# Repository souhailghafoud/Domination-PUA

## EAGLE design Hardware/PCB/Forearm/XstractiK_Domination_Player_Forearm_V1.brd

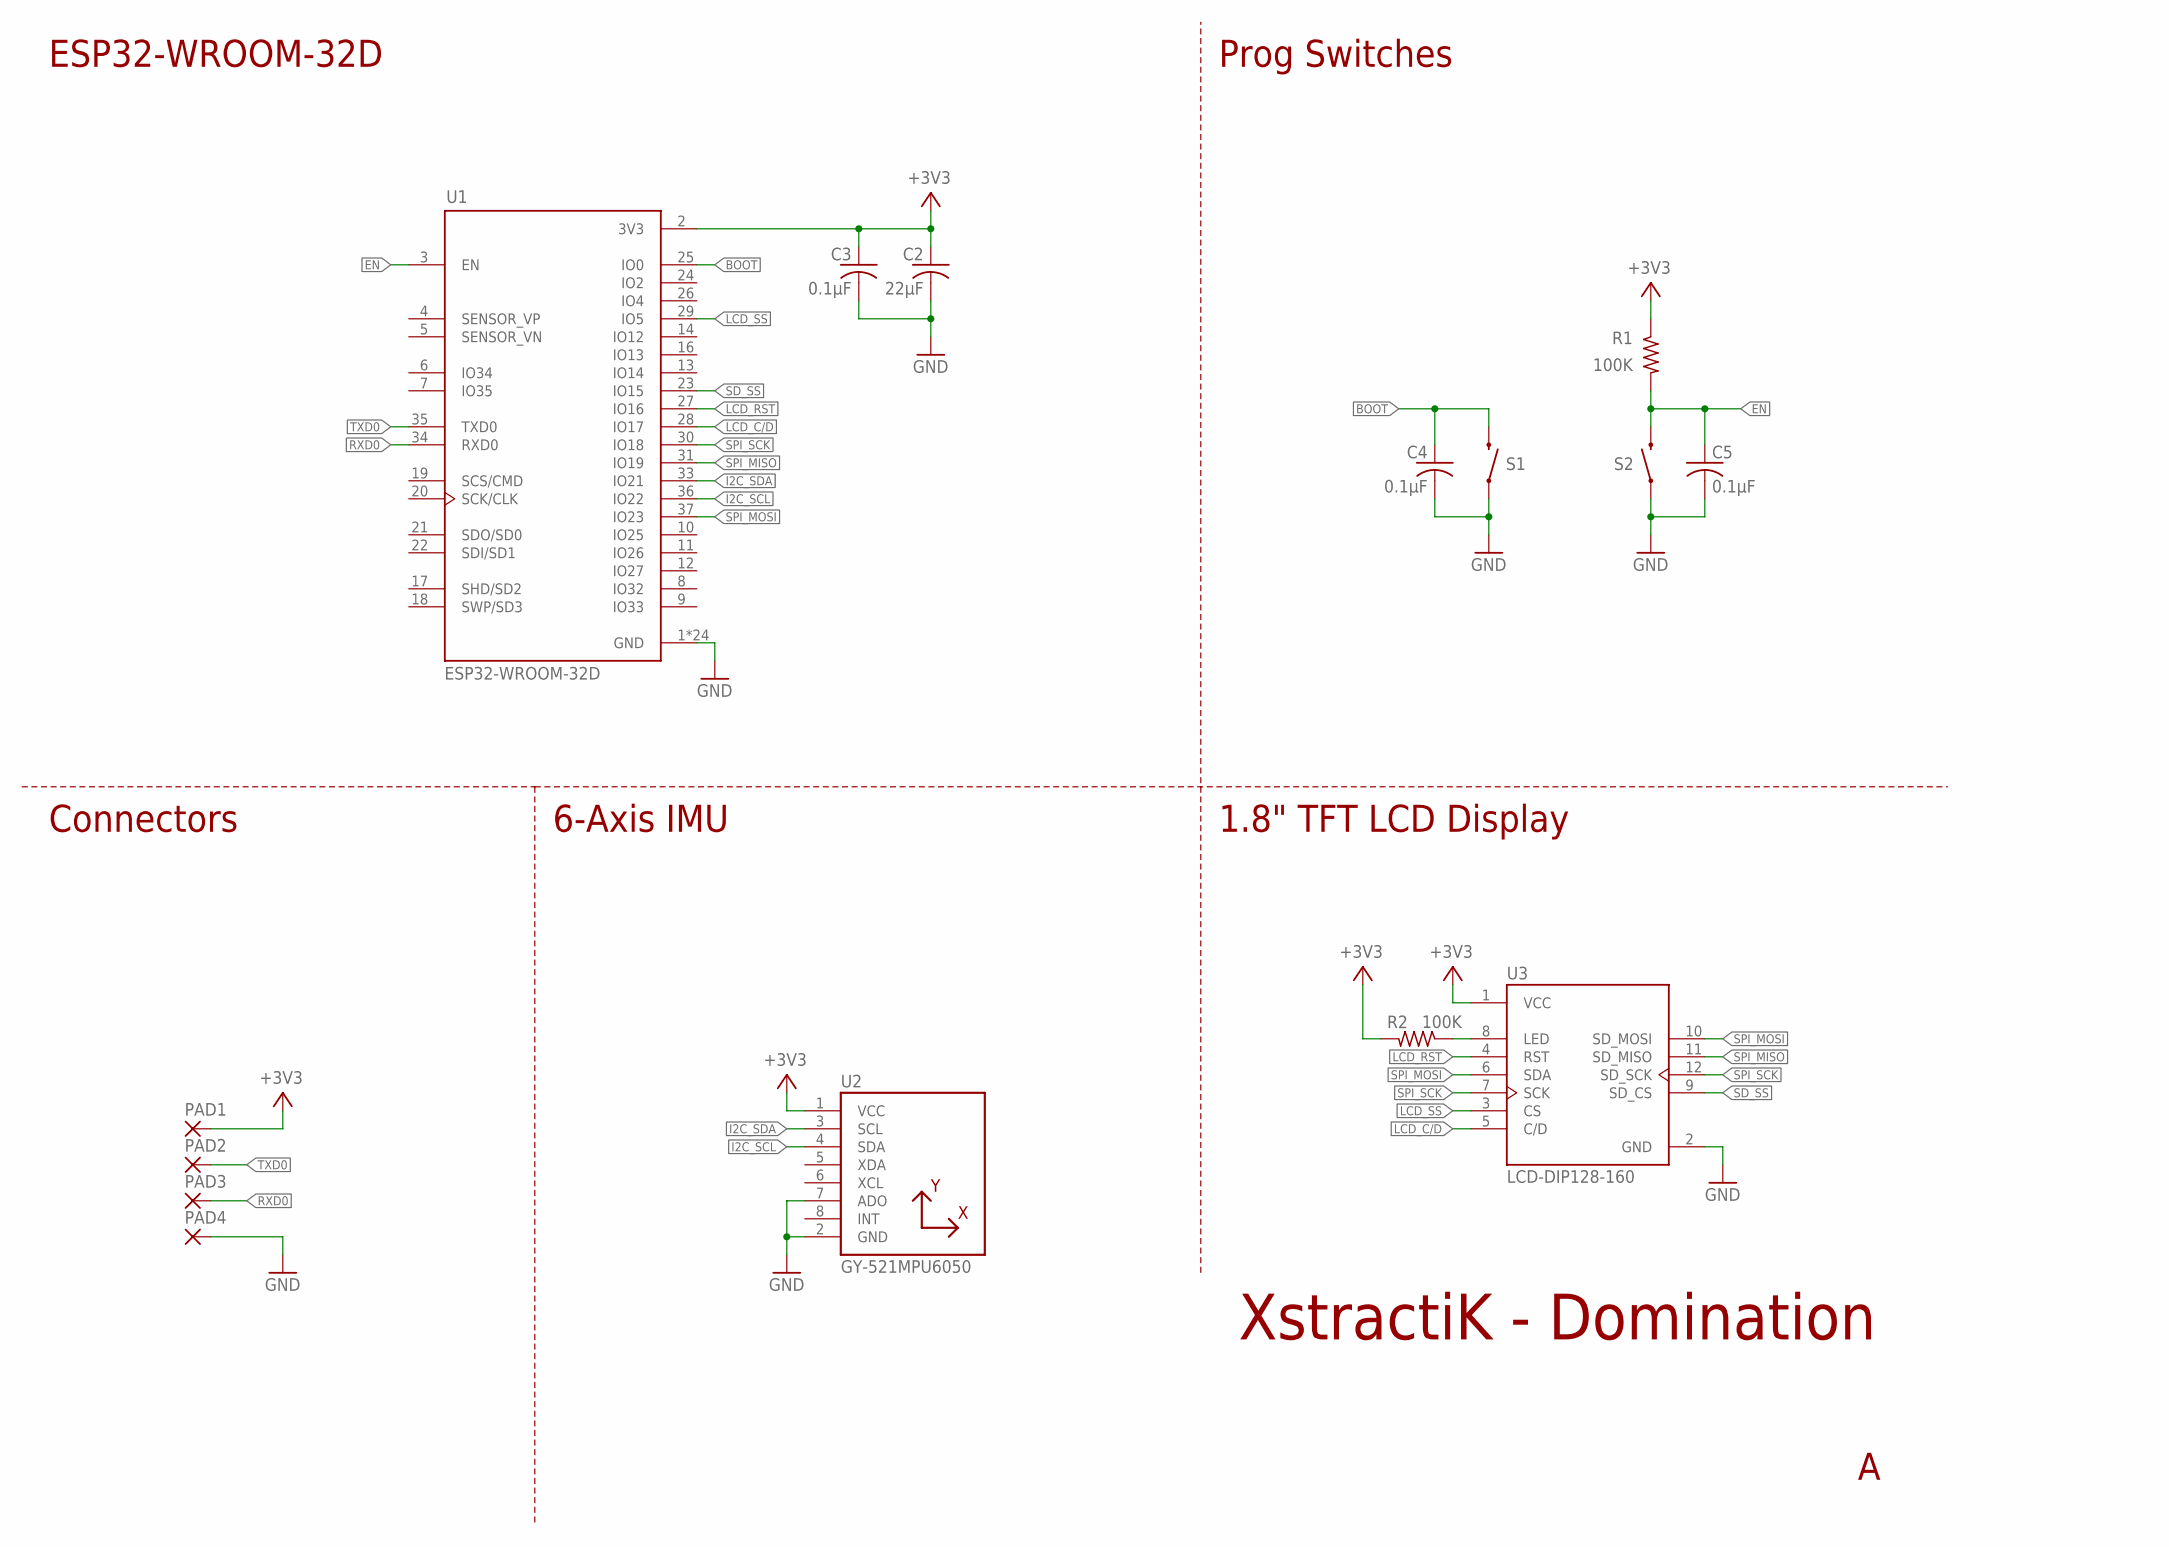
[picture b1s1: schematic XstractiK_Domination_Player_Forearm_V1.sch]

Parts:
C2: 22μF; C0805
C3, C4, C5: 0.1μF; C0805
PAD1, PAD2, PAD3, PAD4: WIREPADSMD5-1,8; 5-1,8
R1, R2: 100K; R0805
S1, S2: MOMENTARY-SWITCH-SPST-SMD-5.2MM-TALL; TACTILE_SWITCH_SMD_5.2MM
U1: ESP32-WROOM-32D; MODULE_ESP32-WROOM-32D
U2: GY-521MPU6050; GY-521
U3: LCD-DIP128-160

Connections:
+3V3: C2.1, C3.1, PAD1.1, R1.1, R2.2, U1.2 (3V3), U2.1 (VCC), U3.1 (VCC)
BOOT: C4.1, S1.3 (2), U1.25 (IO0)
EN: C5.1, R1.2, S2.3 (2), U1.3 (EN)
GND: C2.2, C3.2, C4.2, C5.2, PAD4.1, S1.1, S2.1, U1.1 (GND), U1.15 (GND), U1.38 (GND), U1.39_1 (GND), U1.39_2 (GND), U1.39_3 (GND), U1.39_4 (GND), U1.39_5 (GND), U1.39_6 (GND), U1.39_7 (GND), U1.39_8 (GND), U1.39_9 (GND), U1.39_10 (GND), U1.39_11 (GND), U1.39_12 (GND), U1.39_13 (GND), U1.39_14 (GND), U1.39_15 (GND), U1.39_16 (GND), U1.39_17 (GND), U1.39_18 (GND), U1.39_19 (GND), U1.39_20 (GND), U1.39_21 (GND), U2.2 (GND), U2.7 (ADO), U3.2 (GND)
I2C_SCL: U1.36 (IO22), U2.4 (SDA)
I2C_SDA: U1.33 (IO21), U2.3 (SCL)
LCD_C/D: U1.28 (IO17), U3.5 (C/D)
LCD_LED: R2.1, U3.8 (LED)
LCD_RST: U1.27 (IO16), U3.4 (RST)
LCD_SS: U1.29 (IO5), U3.3 (CS)
RXD0: PAD3.1, U1.34 (RXD0)
SD_SS: U1.23 (IO15), U3.9 (SD_CS)
SPI_MISO: U1.31 (IO19), U3.11 (SD_MISO)
SPI_MOSI: U1.37 (IO23), U3.6 (SDA), U3.10 (SD_MOSI)
SPI_SCK: U1.30 (IO18), U3.7 (SCK), U3.12 (SD_SCK)
TXD0: PAD2.1, U1.35 (TXD0)

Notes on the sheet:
XstractiK - Domination
ESP32-WROOM-32D
Prog Switches
Connectors
6-Axis IMU
1.8" TFT LCD Display

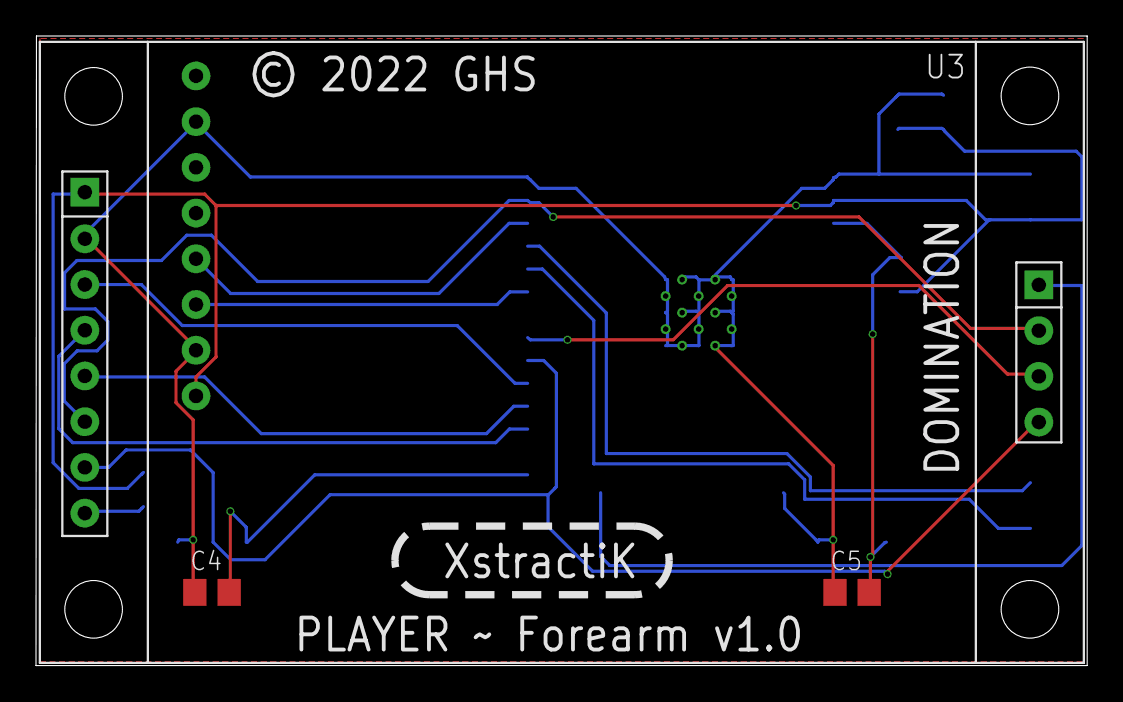
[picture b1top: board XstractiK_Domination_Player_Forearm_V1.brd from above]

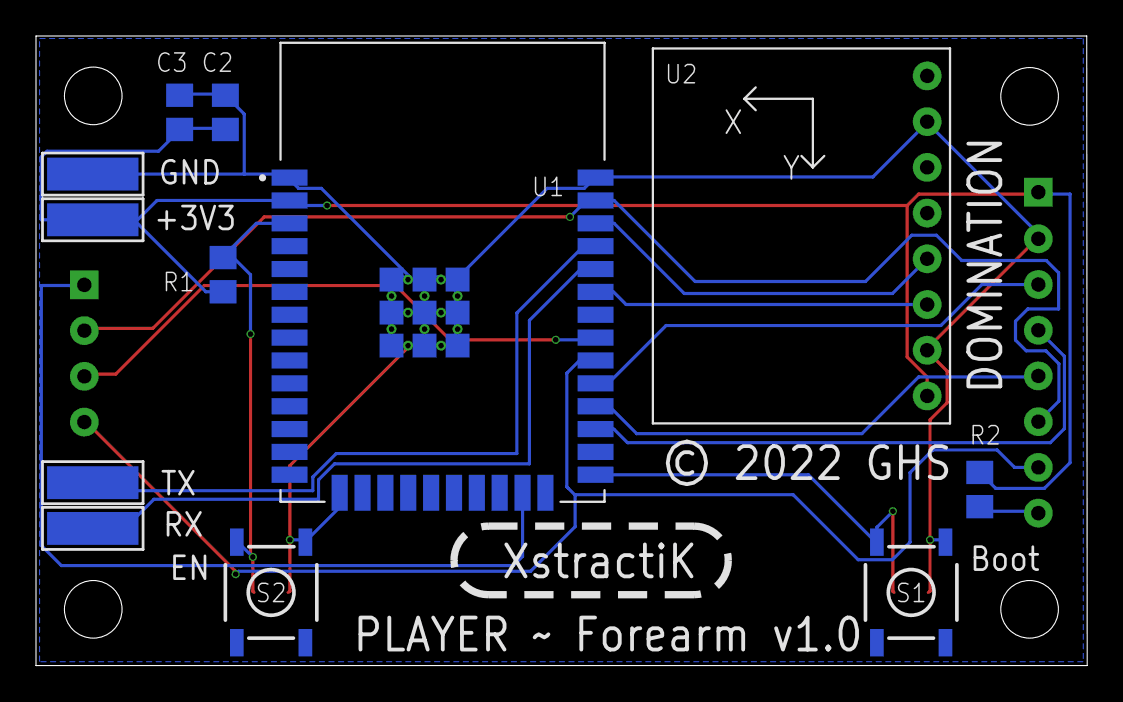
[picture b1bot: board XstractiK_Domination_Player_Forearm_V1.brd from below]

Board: 2 copper layers, 58.4 x 35.0 mm, 15 parts (12 on the bottom side), 16 nets.

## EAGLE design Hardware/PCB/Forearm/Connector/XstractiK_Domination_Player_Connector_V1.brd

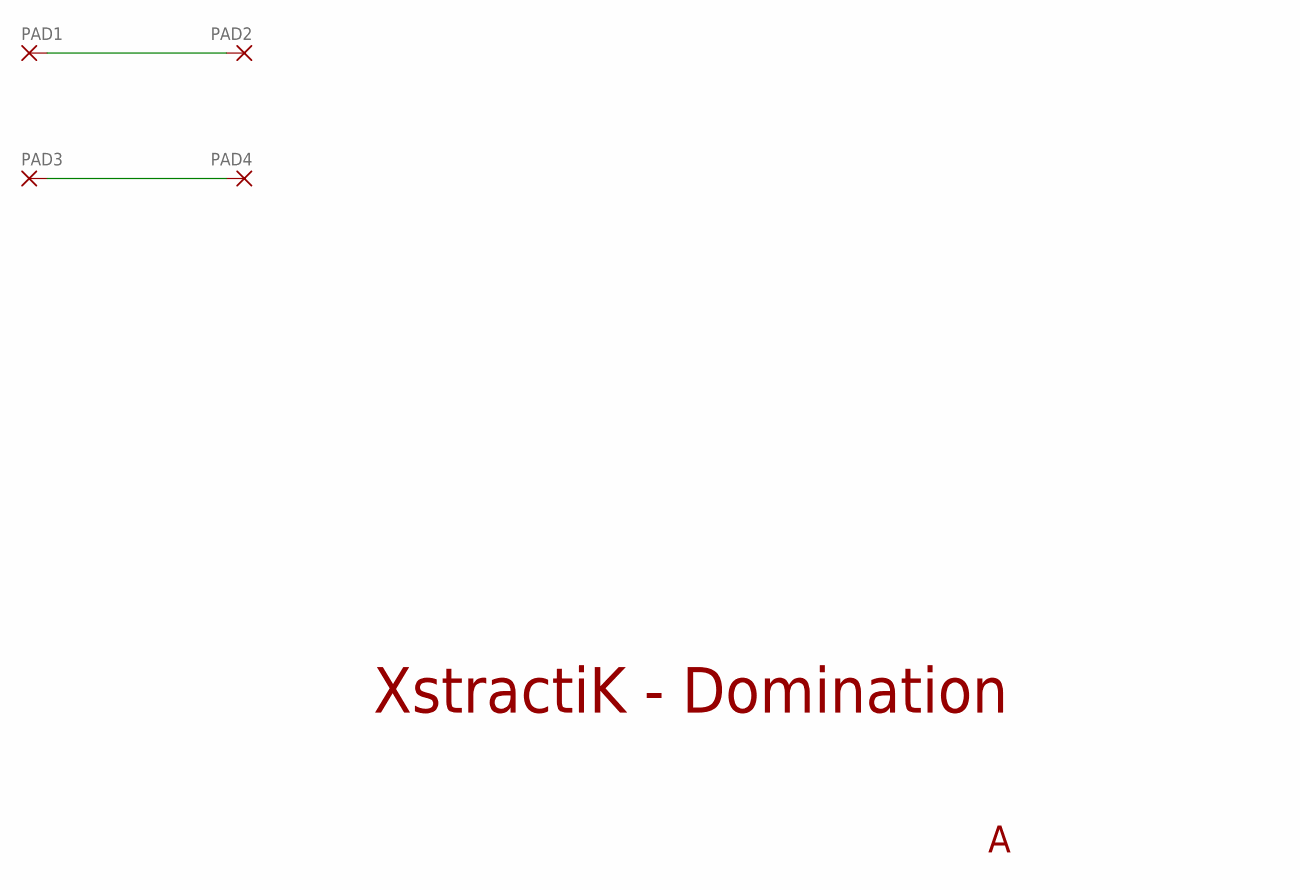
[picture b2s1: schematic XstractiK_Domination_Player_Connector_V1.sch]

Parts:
PAD1, PAD2, PAD3, PAD4: WIREPADSMD1,27-254; SMD1,27-2,54

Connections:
unnamed: PAD1.1, PAD2.1
unnamed: PAD3.1, PAD4.1

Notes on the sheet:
XstractiK - Domination

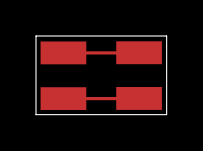
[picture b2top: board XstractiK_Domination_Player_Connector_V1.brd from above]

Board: 2 copper layers, 7.3 x 4.4 mm, 4 parts (0 on the bottom side), 2 nets.

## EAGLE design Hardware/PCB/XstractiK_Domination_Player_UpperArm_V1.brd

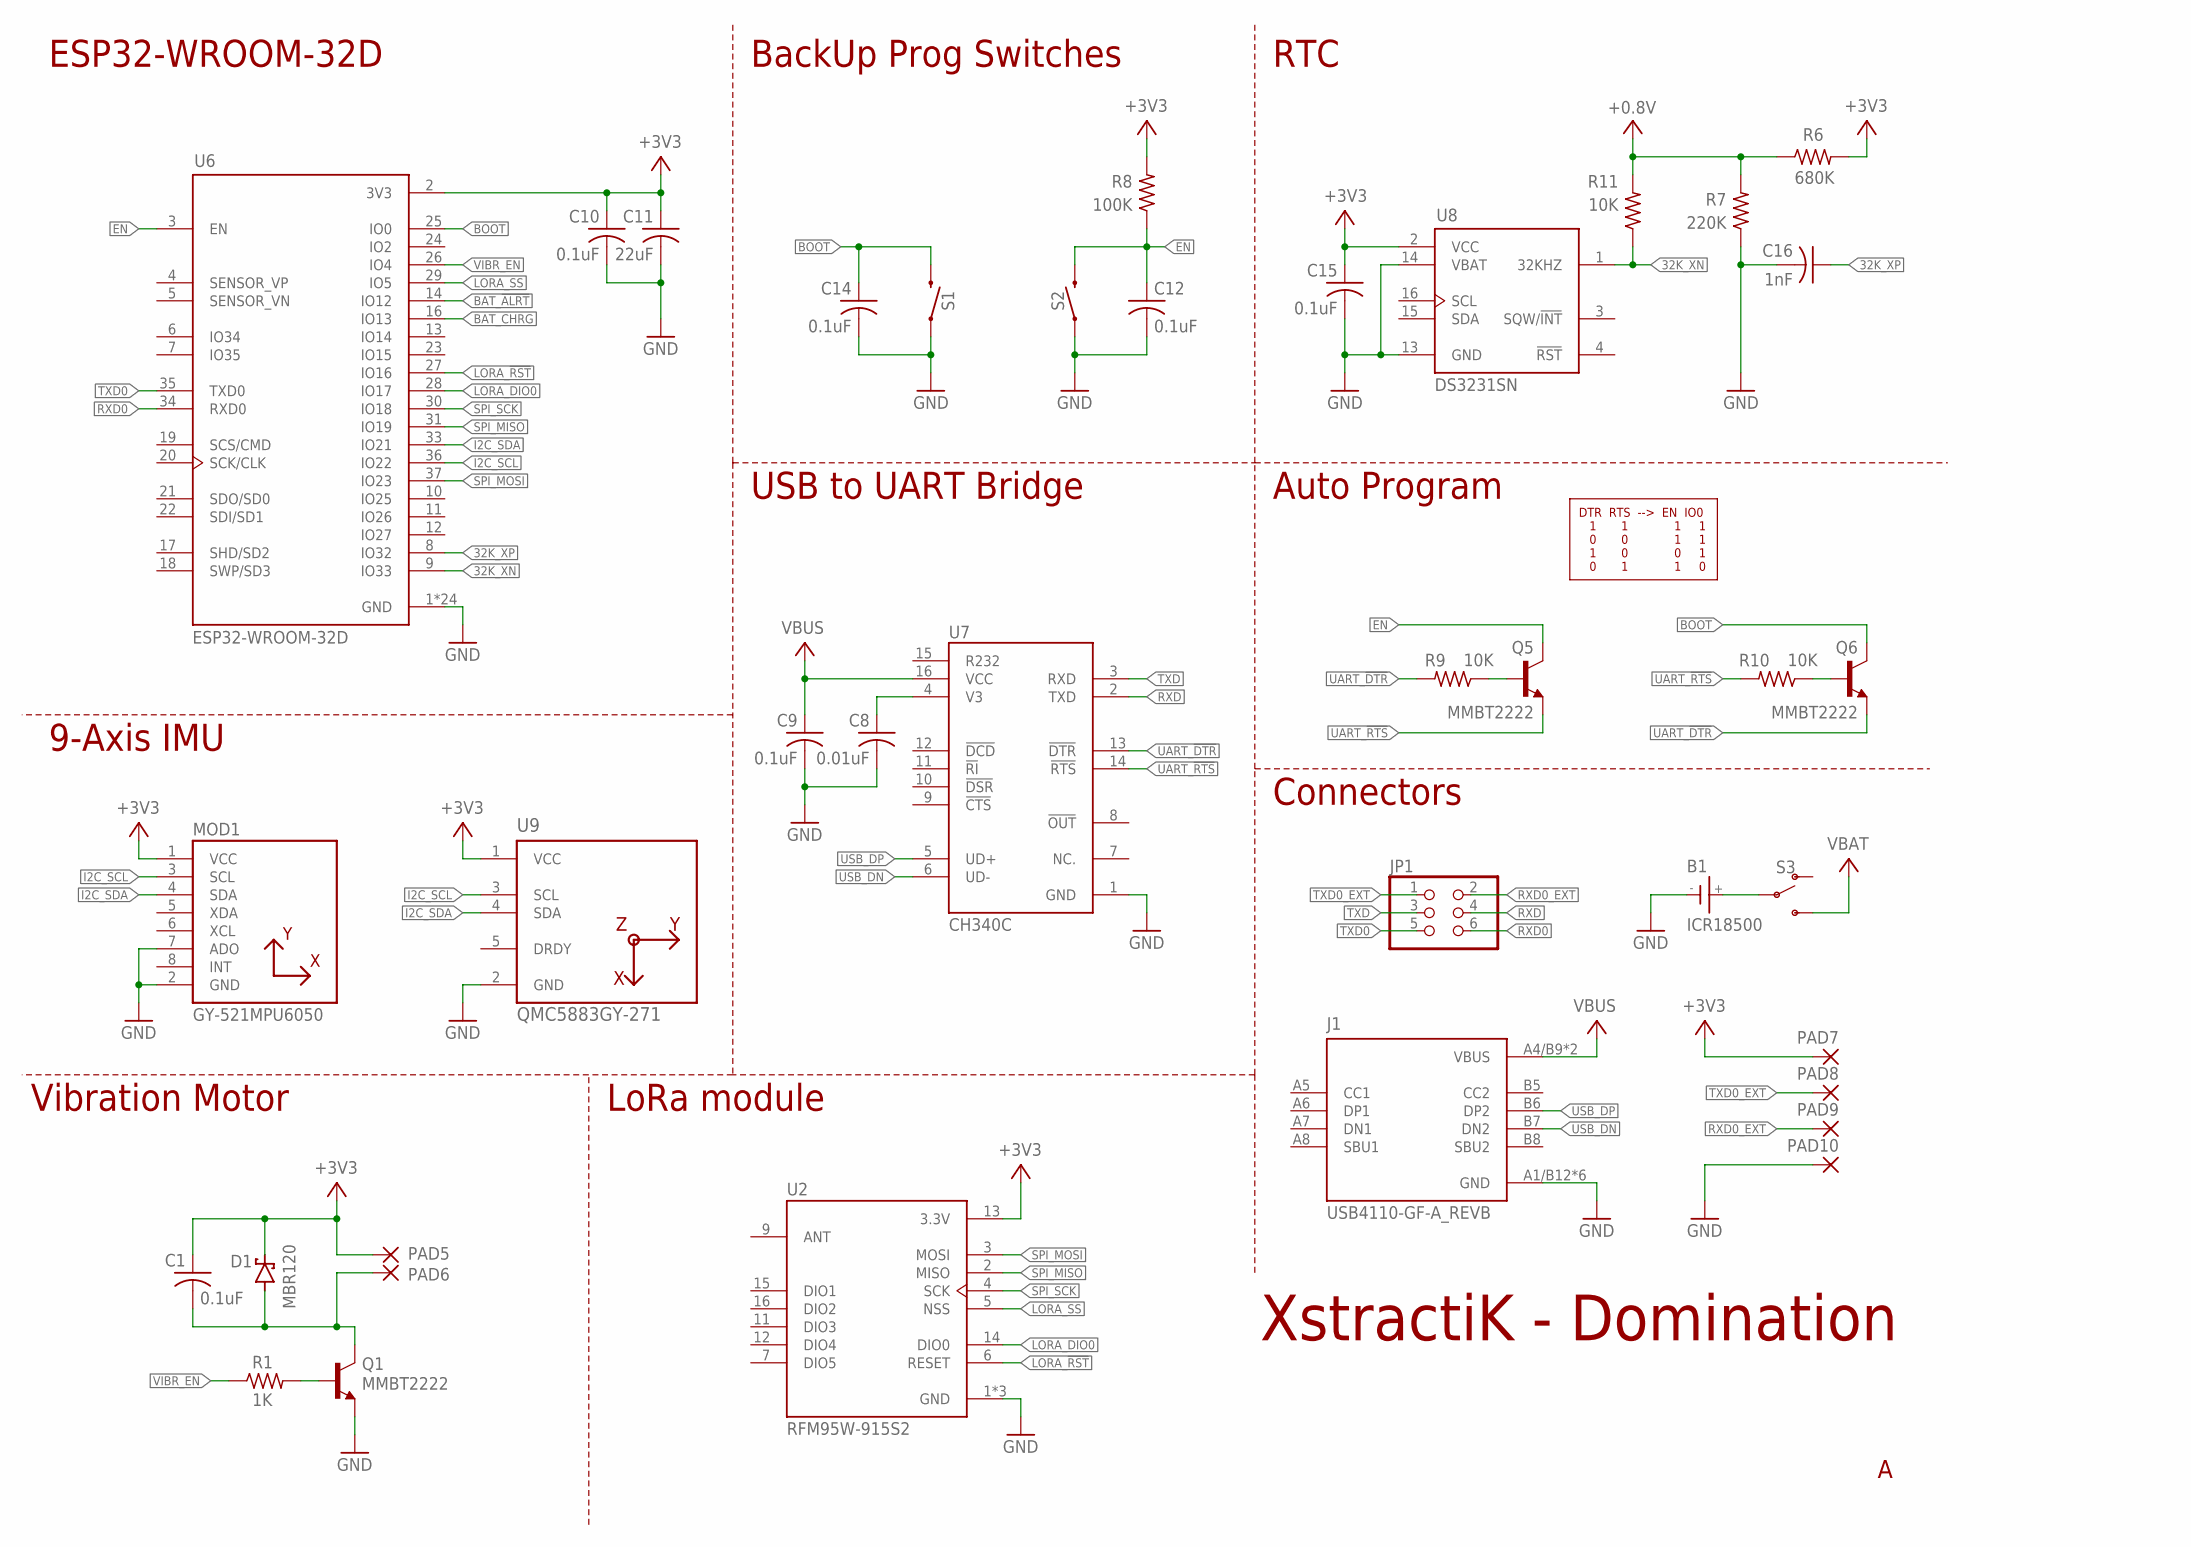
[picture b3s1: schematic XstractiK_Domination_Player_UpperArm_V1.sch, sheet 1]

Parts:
B1: ICR18500
C1, C9, C10, C12, C14, C15: 0.1uF; C0805
C8: 0.01uF; C0805
C11: 22uF; C0805
C16: 1nF; C0805
D1: ON_SEMICONDUCTOR_MBR120VLSFT1GON_SEMICONDUCTOR_MB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; ON_SEMICONDUCTOR_MBR120VLSFT1G_0
J1: USB4110-GF-A_REVB; GCT_USB4110-GF-A_REVB
JP1: PINHD-2X3; 2X03
MOD1: GY-521MPU6050; GY-521
PAD5, PAD6: WIREPAD1,6/0,8; 1,6/0,8
PAD7, PAD8, PAD9, PAD10: WIREPADSMD1,27-254; SMD1,27-2,54
Q1, Q5, Q6: MMBT2222; SOT23-BEC
R1: 1K; R0805
R6: 680K; R0805
R7: 220K; R0805
R8: 100K; R0805
R9, R10, R11: 10K; R0805
S1, S2: MOMENTARY-SWITCH-SPST-SMD-5.2MM-TALL; TACTILE_SWITCH_SMD_5.2MM
S3: SWITCH-SPDT-SMD-RIGHT-ANGLE; SWITCH_SPST_SMD_A
U2: RFM95W-915S2; XCVR_RFM95W-915S2
U6: ESP32-WROOM-32D; MODULE_ESP32-WROOM-32D
U7: CH340C; SOIC127P600X180-16N
U8: DS3231SN; SOIC127P1032X265-16N
U9: QMC5883GY-271; GY-271

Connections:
32K_XN: R11.1, U6.9 (IO33), U8.1 (32KHZ)
32K_XP: C16.1, U6.8 (IO32)
+: B1.+, S3.2
+0.8V: R6.1, R7.2, R11.2
+3V3: C1.1, C10.1, C11.1, C15.1, D1.1 (K), MOD1.1 (VCC), PAD5.1, PAD7.1, R6.2, R8.2, U2.13 (3.3V), U6.2 (3V3), U8.2 (VCC), U9.1 (VCC); also elsewhere on the board
-: B1.-
BAT_!ALRT: U6.14 (IO12); also elsewhere on the board
BAT_CHRG: U6.16 (IO13); also elsewhere on the board
BOOT: C14.1, Q6.C, S1.3 (2), U6.25 (IO0)
EN: C12.1, Q5.C, R8.1, S2.3 (2), U6.3 (EN)
GND: C8.2, C9.2, C10.2, C11.2, C12.2, C14.2, C15.2, C16.2, J1.A1/B12 (GND), J1.B1/A12 (GND), J1.S1 (GND), J1.S2 (GND), J1.S3 (GND), J1.S4 (GND), MOD1.2 (GND), MOD1.7 (ADO), PAD10.1, Q1.E, R7.1, S1.1, S2.1, U2.1 (GND), U2.8 (GND), U2.10 (GND), U6.1 (GND), U6.15 (GND), U6.38 (GND), U6.39_1 (GND), U6.39_2 (GND), U6.39_3 (GND), U6.39_4 (GND), U6.39_5 (GND), U6.39_6 (GND), U6.39_7 (GND), U6.39_8 (GND), U6.39_9 (GND), U6.39_10 (GND), U6.39_11 (GND), U6.39_12 (GND), U6.39_13 (GND), U6.39_14 (GND), U6.39_15 (GND), U6.39_16 (GND), U6.39_17 (GND), U6.39_18 (GND), U6.39_19 (GND), U6.39_20 (GND), U6.39_21 (GND), U7.1 (GND), U8.13 (GND), U8.14 (VBAT), U9.2 (GND); also elsewhere on the board
I2C_SCL: MOD1.3 (SCL), U6.36 (IO22), U9.3 (SCL); also elsewhere on the board
I2C_SDA: MOD1.4 (SDA), U6.33 (IO21), U9.4 (SDA); also elsewhere on the board
LORA_!RST: U2.6 (RESET), U6.27 (IO16)
LORA_DIO0: U2.14 (DIO0), U6.28 (IO17)
LORA_SS: U2.5 (NSS), U6.29 (IO5)
M-: C1.2, D1.2 (A), PAD6.1, Q1.C
unnamed: Q1.B, R1.2
unnamed: Q6.B, R10.1
unnamed: Q5.B, R9.1
RXD: JP1.4, U7.2 (TXD)
RXD0: JP1.6, U6.34 (RXD0)
RXD0_EXT: JP1.2, PAD9.1
SPI_MISO: U2.2 (MISO), U6.31 (IO19)
SPI_MOSI: U2.3 (MOSI), U6.37 (IO23)
SPI_SCK: U2.4 (SCK), U6.30 (IO18)
TXD: JP1.3, U7.3 (RXD)
TXD0: JP1.5, U6.35 (TXD0)
TXD0_EXT: JP1.1, PAD8.1
UART_!DTR: Q6.E, R9.2, U7.13 (!DTR)
UART_!RTS: Q5.E, R10.2, U7.14 (!RTS)
USB_DN: J1.B7 (DN2), U7.6 (UD-)
USB_DP: J1.B6 (DP2), U7.5 (UD+)
V3: C8.1, U7.4 (V3)
VBAT: S3.3 (S); also elsewhere on the board
VBUS: C9.1, J1.A4/B9 (VBUS), J1.B4/A9 (VBUS), U7.16 (VCC); also elsewhere on the board
VIBR_EN: R1.1, U6.26 (IO4)

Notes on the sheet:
XstractiK - Domination
Connectors
ESP32-WROOM-32D
Vibration Motor
LoRa module
USB to UART Bridge
Auto Program
RTC
BackUp Prog Switches
DTR RTS --> EN IO0 1 1 1 1 0 0 1 1 1 0 0 1 0 1 1 0
9-Axis IMU

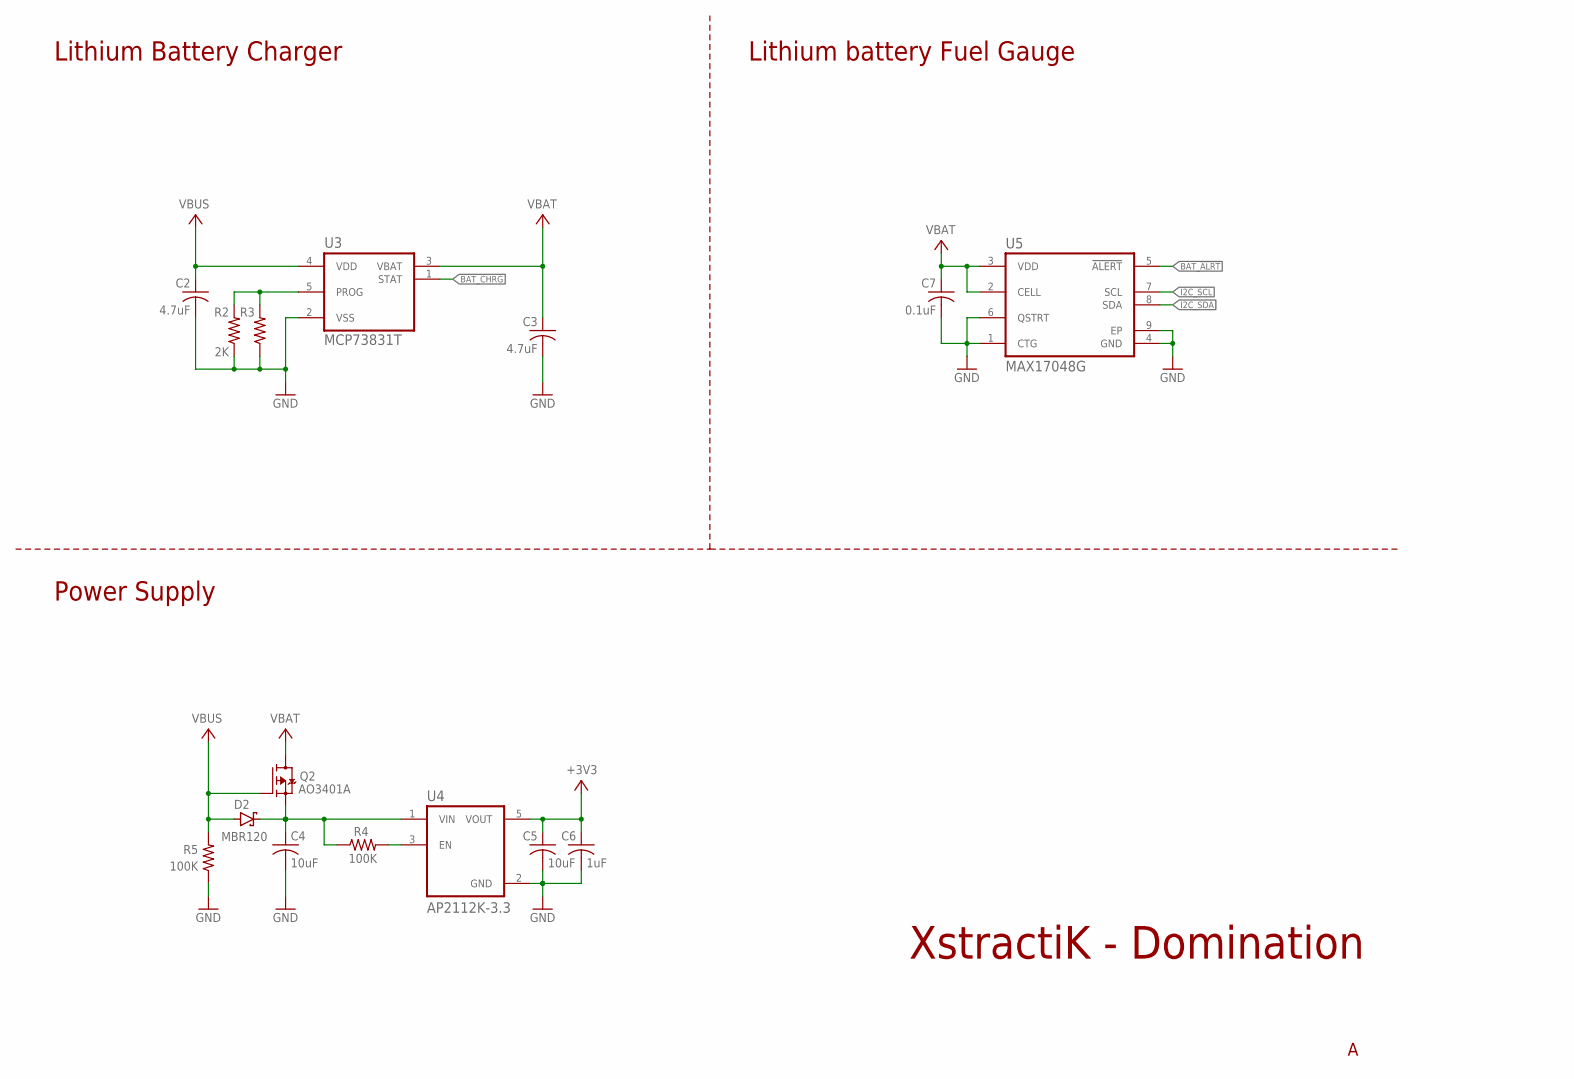
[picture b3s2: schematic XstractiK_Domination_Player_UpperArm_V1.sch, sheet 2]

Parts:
C2, C3: 4.7uF; C0805
C4, C5: 10uF; C0805
C6: 1uF; C0805
C7: 0.1uF; C0805
D2: ON_SEMICONDUCTOR_MBR120VLSFT1GON_SEMICONDUCTOR_MB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; ON_SEMICONDUCTOR_MBR120VLSFT1G_0
Q2: AO3401A; SOT23-3
R2: 2K; R0805
R3: R-US_R0805; R0805
R4, R5: 100K; R0805
U3: MCP73831T; SOT95P270X145-5N
U4: AP2112K-3.3; SOT95P285X140-5N
U5: MAX17048G; SON50P200X200X80-9N

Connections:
+3V3: C5.1, C6.1, U4.5 (VOUT); also elsewhere on the board
BAT_!ALRT: U5.5 (!ALERT); also elsewhere on the board
BAT_CHRG: U3.1 (STAT); also elsewhere on the board
CHRG_PROG: R2.2, R3.2, U3.5 (PROG)
GND: C2.2, C3.2, C4.2, C5.2, C6.2, C7.2, R2.1, R3.1, R5.1, U3.2 (VSS), U4.2 (GND), U5.1 (CTG), U5.4 (GND), U5.6 (QSTRT), U5.9 (EP); also elsewhere on the board
I2C_SCL: U5.7 (SCL); also elsewhere on the board
I2C_SDA: U5.8 (SDA); also elsewhere on the board
REG_EN: R4.2, U4.3 (EN)
REG_VIN: C4.1, D2.1 (K), Q2.2 (S), R4.1, U4.1 (VIN)
VBAT: C3.1, C7.1, Q2.3 (D), U3.3 (VBAT), U5.2 (CELL), U5.3 (VDD); also elsewhere on the board
VBUS: C2.1, D2.2 (A), Q2.1 (G), R5.2, U3.4 (VDD); also elsewhere on the board

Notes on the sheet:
Lithium Battery Charger
Power Supply
Lithium battery Fuel Gauge
XstractiK - Domination

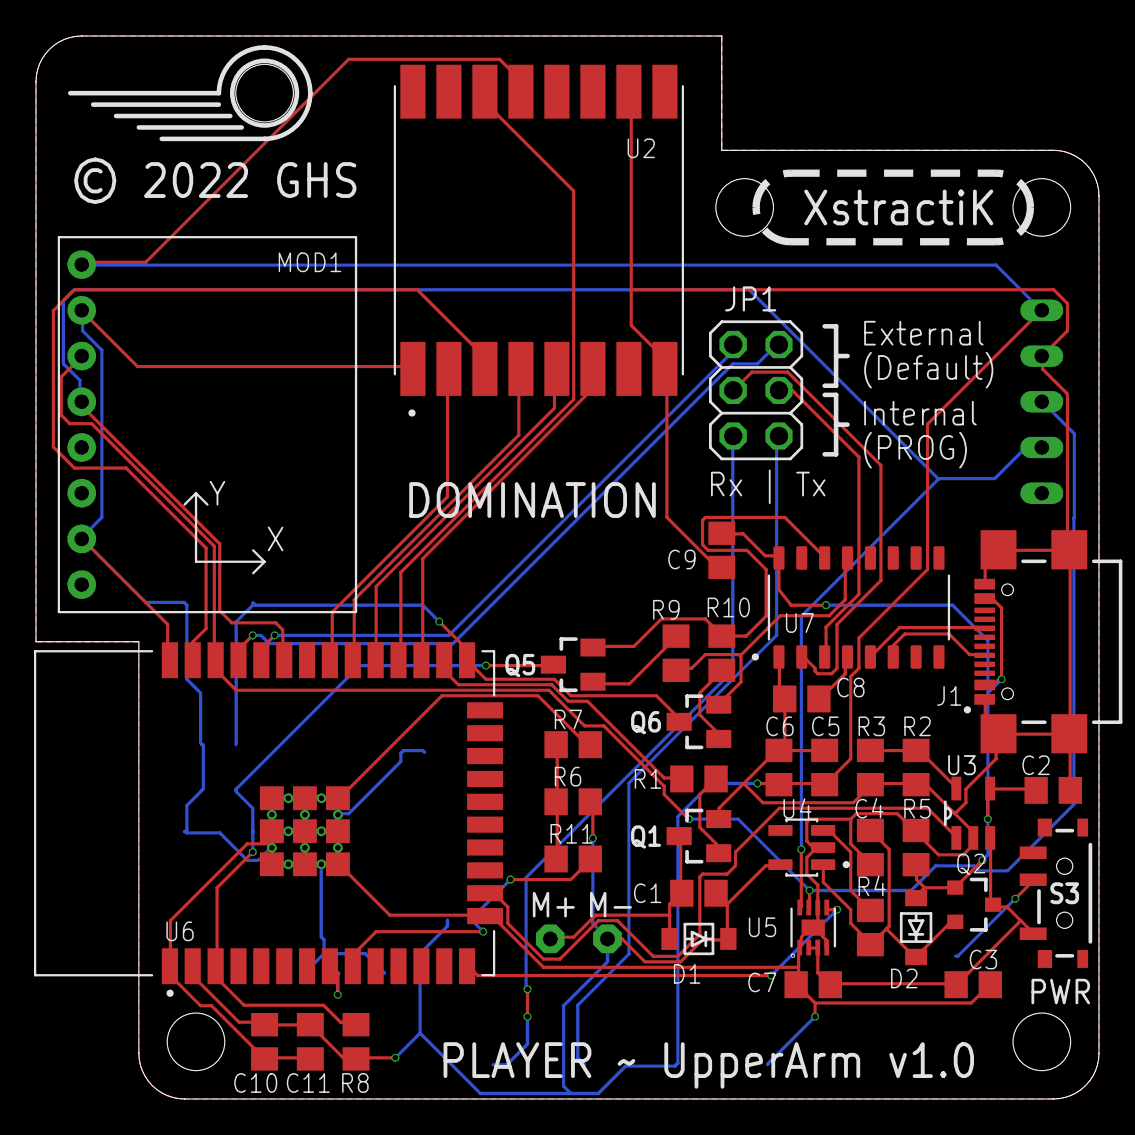
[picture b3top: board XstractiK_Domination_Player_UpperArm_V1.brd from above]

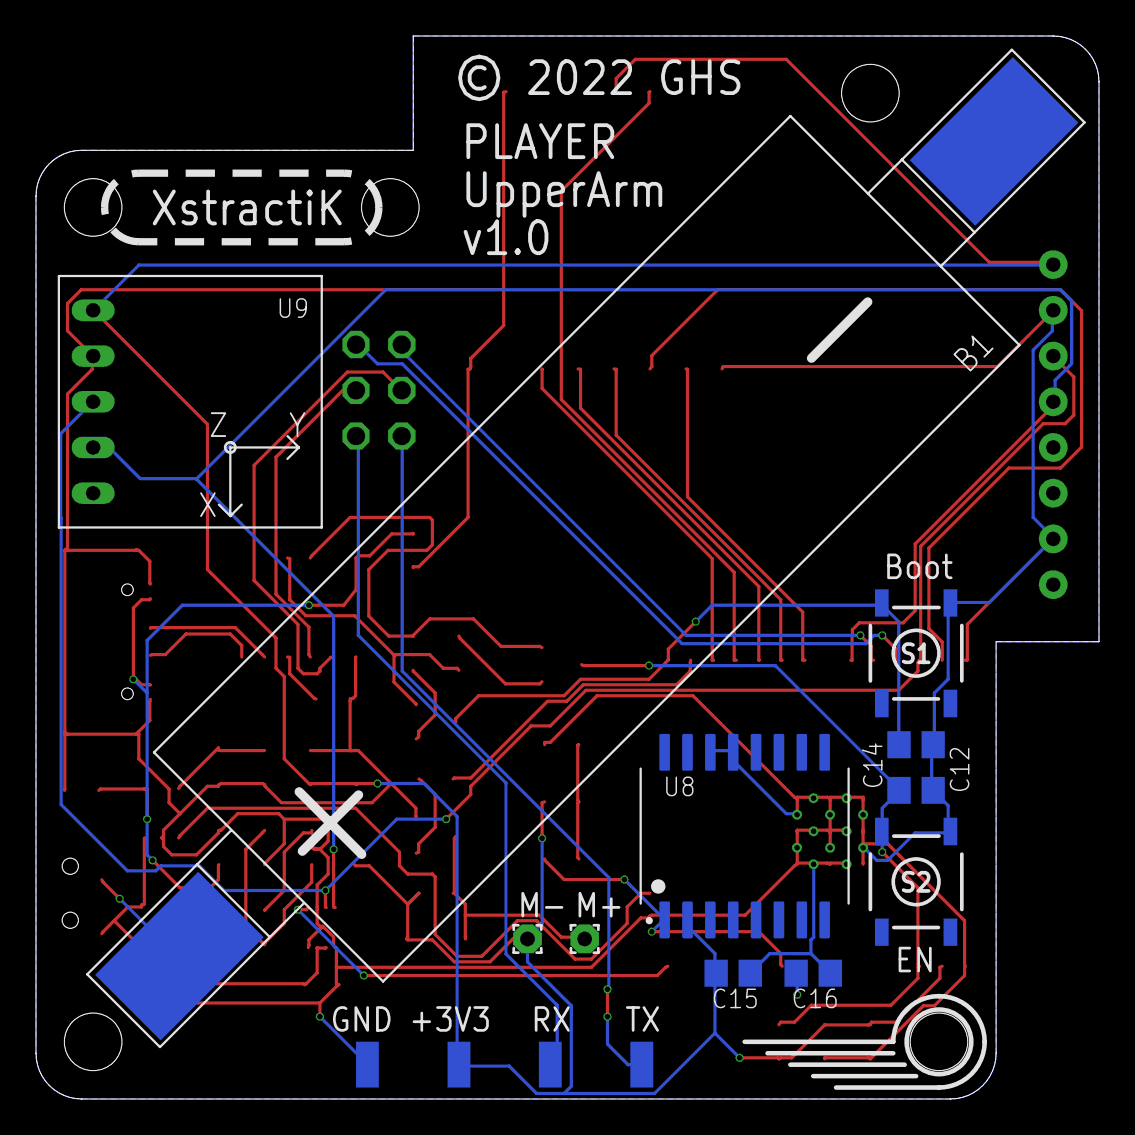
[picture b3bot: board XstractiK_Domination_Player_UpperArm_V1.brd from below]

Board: 2 copper layers, 59.1 x 59.1 mm, 53 parts (15 on the bottom side), 39 nets.

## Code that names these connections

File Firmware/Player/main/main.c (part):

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#define LOW 			                0

/* I2C pins */
#define PIN_I2C_SCL                     GPIO_NUM_22
#define PIN_I2C_SDA                     GPIO_NUM_21

/* SPI pins */
#define PIN_SPI_MOSI                    GPIO_NUM_23
#define PIN_SPI_MISO                    GPIO_NUM_19
#define PIN_SPI_CLK                     GPIO_NUM_18

/* LoRa pins */
#define PIN_LORA_SS                     GPIO_NUM_5
#define PIN_LORA_DIO0                   GPIO_NUM_17
#define PIN_LORA_RESET                  GPIO_NUM_16

/* Vibration Motor pins */
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    s_cp_notif_irq_semaphore = xSemaphoreCreateBinary();

    /* Set LoRa DIO0 pin as interrupt pin for CP notification events */
    gpio_set_direction(PIN_LORA_DIO0, GPIO_MODE_INPUT);     // Input mode
    gpio_set_intr_type(PIN_LORA_DIO0, GPIO_INTR_POSEDGE);   // Rising edge interrupt

    /* Setup ISR on LoRa DIO0 pin for CP notification events */
    gpio_install_isr_service(ESP_INTR_FLAG_LEVEL3);
    gpio_isr_handler_add(PIN_LORA_DIO0, cp_notif_irq_isr, (void *)PIN_LORA_DIO0);
    
    /* Preamble in CP notifications */
    strcat(cp_notif_preamble, FIRMWARE_VERSION);
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    printf("**********************************************\n\n");
    
    /* Init I2C Peripheral */
    if (ESP_OK != i2c_init(PIN_I2C_SDA, PIN_I2C_SCL)) {
        printf("I2C init error\n\n");
    }

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
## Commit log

2021-11-16 .gitignore update
    Remove sdkconfig files
2021-11-16 Project files
2022-04-06 LoRa driver
    Send & receive packets fully operational (Tested)
2022-04-06 Receive CP status changes over LoRa
    Receive CP status changes from CP :
    - When CP was captured
    - When CP capture is in progress
    LoRa packet frame :
    - cp_id:%d, cp_status:%d, dominant_team:%d
    LoRa packet frame content :
2022-04-08 Code refactor + LoRa packets length increase
    - Code refactor
    - LoRa packets length increased to 40
2022-04-24 Add datasheets
    - Coin flat vibration motor
    - ESP32 DevKitC V4
    - ESP32-WROOM-32D/U
    - RFM95W
    - MPU6050
2022-04-24 Add Eagle libraries
    - ESP32-DEVKITC-32U/D
    - ESP32-WROOM-32D
    - MPU6050
    - RFM95W
2022-04-24 Add schematic + Eagle libraries + datasheets
    Schematic :
    - ESP32 (DevKitC-32D)
    - IMU (MPU6050)
    - LoRa module (RFM95W)
    - Vibration motor
    - LiPo battery charger (MCP73831T)
2022-04-26 Schematic + Libraries + Datasheets
    Schematic :
    - Li-Ion battery fuel gauge (MAX17048G)
    - USB to UART bridge (CH340C)
    - Connectors for USB-C, Breakout pins, Li-Ion battery
    - Mount holes
    Libraries :
2022-04-26 Reallocate pins + Add vibration motor
    Reallocate pins :
    - I2C
    - LoRa
    Vibration motor :
    - Vibrate when
    - the player's device is initialized (2x for 0.5sec)
2022-04-29 Add RTC Clock 32.768 kHz
    DS3231 used as external RTC clock for ESP32
2022-05-01 Vibration + BLE + Code Refactor
    Vibration :
    - Create task in init function
    - Add queue for vibration enable requests
    BLE :
    - Add BLE files into Comms component (ble.c ble.h)
    - Add EventGroup for callbacks
2022-05-02 Player Status + Crash Fix + Code Refactor
    Player Status :
    - CP scan removed
    Crash Fix :
    - Missing semi-colon in I2C header file
2022-05-02 Schematic + Library + Datasheet
    Add 3-axis Magnetic sensor module (HMC5883)
2022-05-24 Schematic and PCB
    UpperArm and Forearm designs
2022-05-24 Enclosure 3D design
    UpperArm and Forearm
2022-05-24 New Firmware sub-directories
    UpperArm and Forearm
2022-05-24 Remove Firmware directory
2022-05-25 Add IMU filtering algorithm + Code refactor
    Filter MPU6050 accelerometer and gyroscope data with Madgwick algorithm to generate quaternions and Euler angles
2022-05-30 Change project name
2022-05-30 Remove Forearm firmware from repo
2022-05-30 Remove Forearm hardware files from repo

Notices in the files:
Firmware/Player/main/main.c:
@copyright Copyright © 2021 GHS-Tech. All rights reserved.
Hardware/PCB/Forearm/XstractiK_Domination_Player_Forearm_V1.brd:
© 2022 GHS
parts and their libraries:
Switches: Licensing: Creative Commons ShareAlike 4.0 International - https://creativecommons.org/licenses/by-sa/4.0
